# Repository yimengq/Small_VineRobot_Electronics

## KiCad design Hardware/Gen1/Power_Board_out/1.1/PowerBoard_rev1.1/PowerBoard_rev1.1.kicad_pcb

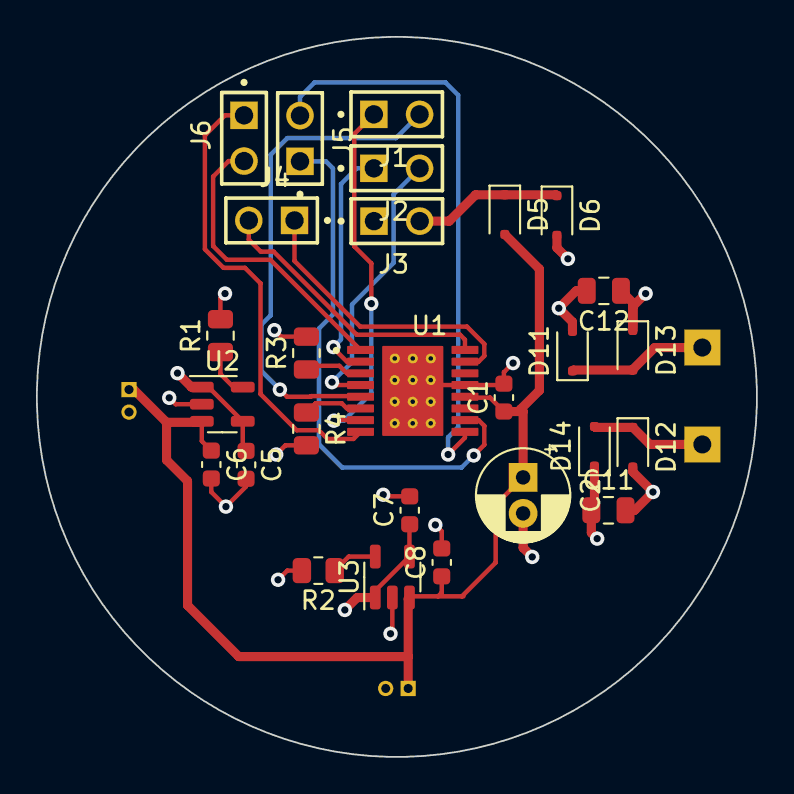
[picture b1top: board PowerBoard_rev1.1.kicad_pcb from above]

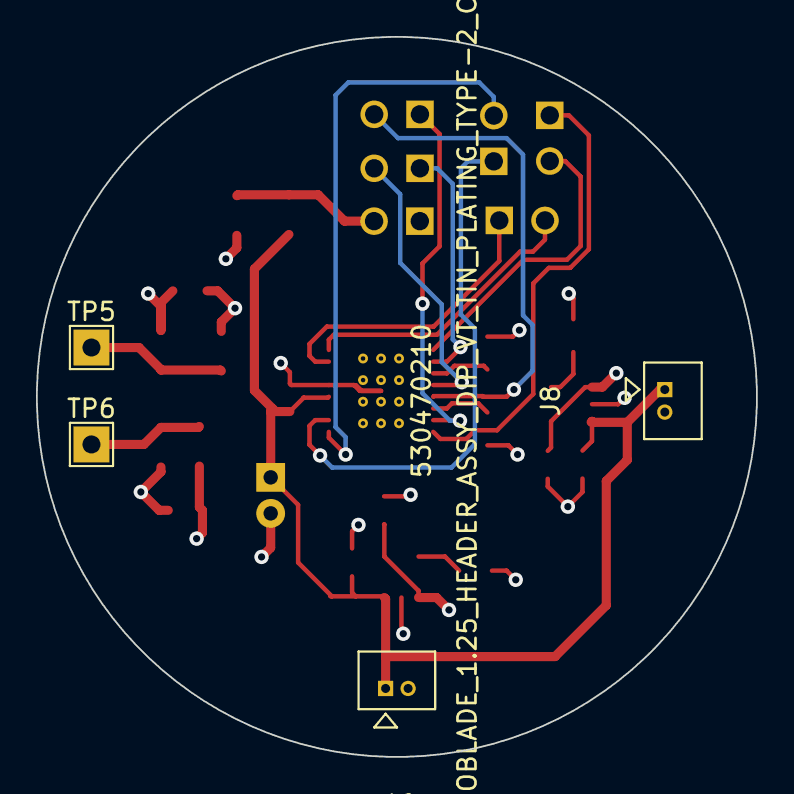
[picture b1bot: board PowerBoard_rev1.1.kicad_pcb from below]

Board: 4 copper layers, 40.0 x 40.0 mm, 31 parts (4 on the bottom side), 20 nets.

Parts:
C1: 100nF; C_0603_1608Metric
C2: 10uF; CP_Radial_D5.0mm_P2.00mm
C5, C6, C7, C8: 1uF; C_0603_1608Metric
C11: 6nF; C_0805_2012Metric
C12: 10uF; C_0805_2012Metric
D5, D6, D11, D12, D13, D14: PMEG6010CEJ; D_SOD-323F
J1, J2, J3, J4, J5, J6: HMTSW-102-X-X-S-X; SAMTEC_HMTSW-102-X-X-S-X
J7, J8: 530470210; CON_530470210_MOL
R1, R2: 2k; R_0805_2012Metric
R3, R4: 2; R_0805_2012Metric
TP5: COIL1; TestPoint_THTPad_2.0x2.0mm_Drill1.0mm
TP6: COIL2; TestPoint_THTPad_2.0x2.0mm_Drill1.0mm
U1: DRV8410PWPR; IC_DRV8410PWPR
U2, U3: MCP73812T-420I-OT; SOT-23-5

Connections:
+BATT: C1.1, C2.1, C6.1, C8.1, D5.2 (A), J7.1, J8.1, U1.12 (VM), U2.3 (V_{BAT}), U3.3 (V_{BAT})
DRV_FAULT: J6.01, U1.8 (~FAULT)
DRV_SLEEP: J6.02, U1.1 (~SLEEP)
GND: C1.2, C2.2, C5.2, C6.2, C7.2, C8.2, C11.2, C12.2, D11.2 (A), D12.2 (A), J3.01, J7.2, J8.2, R1.2, R2.2, R3.2, R4.2, U1.13 (GND), U1.17 (EXP), U2.2 (V_{SS}), U3.2 (V_{SS})
MOTOR1_AIN1: J4.02, U1.16 (AIN1)
MOTOR1_AIN2: J4.01, U1.15 (AIN2)
MOTOR2_BIN1: J5.02, U1.9 (BIN1)
MOTOR2_BIN2: J5.01, U1.10 (BIN2)
unnamed: D11.1 (K), D13.2 (A), TP5.1
unnamed: D12.1 (K), D14.2 (A), TP6.1
unnamed: R3.1, U1.3 (AISEN)
unnamed: J2.01, U1.2 (AOUT1)
unnamed: J2.02, U1.4 (AOUT2)
unnamed: R4.1, U1.6 (BISEN)
unnamed: J1.01, U1.7 (BOUT1)
unnamed: J1.02, U1.5 (BOUT2)
unnamed: R1.1, U2.5 (PROG)
unnamed: R2.1, U3.5 (PROG)
VCC: C5.1, C7.1, C11.1, C12.1, D6.2 (A), D13.1 (K), D14.1 (K), U2.1 (CE), U2.4 (V_{DD}), U3.1 (CE), U3.4 (V_{DD})
VDC: D5.1 (K), D6.1 (K), J3.02

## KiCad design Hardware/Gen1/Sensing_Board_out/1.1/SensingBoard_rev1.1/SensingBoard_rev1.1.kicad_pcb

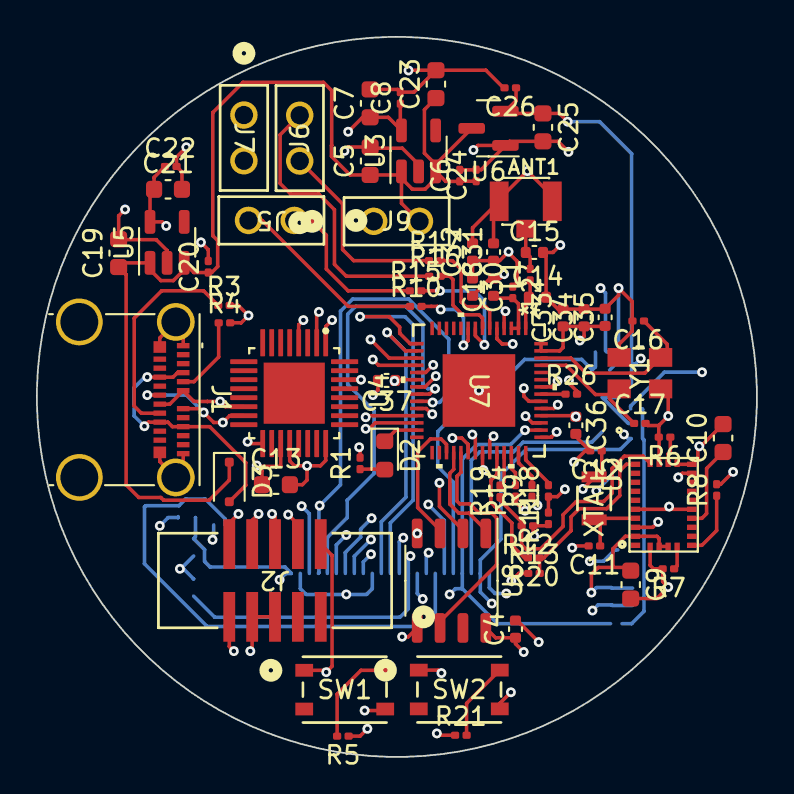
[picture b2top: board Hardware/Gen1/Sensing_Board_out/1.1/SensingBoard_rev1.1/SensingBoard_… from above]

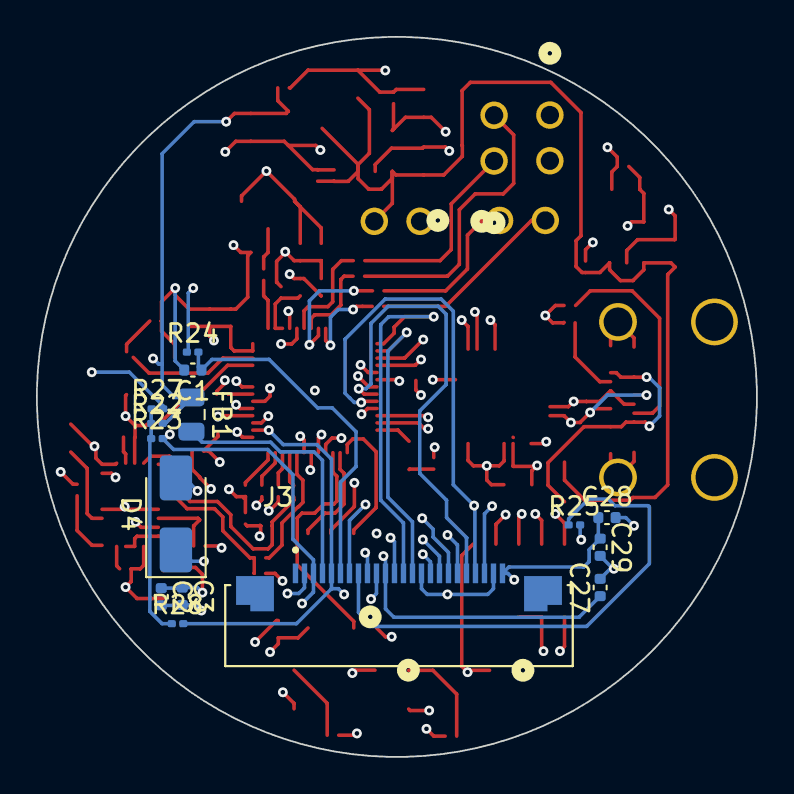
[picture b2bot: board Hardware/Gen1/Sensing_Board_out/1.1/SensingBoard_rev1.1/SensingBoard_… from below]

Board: 6 copper layers, 40.0 x 40.0 mm, 89 parts (15 on the bottom side), 74 nets.

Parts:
ANT1: U.FL-R-SMT-1
C1, C2, C4, C18, C29, C30, C34, C36, C37: 100nF; C_0402_1005Metric
C3: 4.7uF; C_0402_1005Metric
C5, C7, C13, C19, C21, C23, C25: 10uF; C_0603_1608Metric
C6, C8, C20, C22, C24, C26: 1uF; C_0201_0603Metric
C9, C10: 0.1uF; C_0603_1608Metric
C11, C12: 22pF; C_0201_0603Metric
C14, C15: 1.6pF; C_0402_1005Metric
C16, C17: 18pF; C_0201_0603Metric
C27, C28, C31, C32, C33: 2.2uF; C_0402_1005Metric
C35: 10nF; C_0402_1005Metric
D2: LED; LED_0603_1608Metric
D3: PMEG6010CEJ; D_SOD-323F
D4: B140-E3; D_SMA
FB1: 120R-3A; C_0805_2012Metric
J1: USB_C_Receptacle; USB_C_Receptacle_Molex_105450-0101-L
J2: 3221-10-0300-00; CONN10_3221-10-0300-00_CNC
J3: F32R-1A7H1-11024; AMPHENOL_F32R-1A7H1-11024
J5, J6, J7, J9: RS1-02-G; CONN_RS1-02-G_ADM
L1, L2: 2nH; L_0201_0603Metric
R1: 100; R_0201_0603Metric
R3: 6.1K; R_0201_0603Metric
R4: 5.1K; R_0201_0603Metric
R5, R6, R7, R8, R11, R12, R13, R21, R24, R25: 10k; R_0201_0603Metric
R9, R10, R14, R15, R16, R17, R18, R19, R20, R22, R27: 0k; R_0201_0603Metric
R23, R28: 4.7k; R_0201_0603Metric
R26: 499; R_0201_0603Metric
SW1, SW2: PTS815 SJM 250 SMTR LFS; SW4_PTS815 SJM 250 SMTR LFS_CNK
U2: BNO055; LGA28R50P4X10_380X520X100
U3: MIC5504-3.3YM5; SOT-23-5
U4: FT232RQ; QFN50P500X500X90-33N
U5: MIC5504-1.8YM5; SOT-23-5
U6: MCP1700x-280xxTT; SOT-23
U7: ESP32-S3; QFN56_7X7_EXP
U8: GD25D05CT; SOP-8_3.9x4.9mm_P1.27mm
XTAL2: ABS07-32.768KHZ-7-T; XTAL_ABS07-32.768KHZ-7-T_ABR
Y1: ABM8G-40.000MHZ-18-D2Y-T; CRYSTAL_ABM8G_ABR

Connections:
+1V8: C21.1, C22.1, J3.10, U5.5 (VOUT)
+2V8: C25.1, C26.1, C27.1, D4.2 (A), FB1.1, J3.11, R22.2, U6.2 (VO)
+3.3V: C2.1, C3.1, C4.1, C7.1, C8.1, C9.1, C13.1, C30.1, C31.1, C32.1, C33.1, C34.1, C35.1, C36.1, C37.1, J2.5, L2.1, R1.2, R5.1, R11.1, R12.1, R13.1, R21.1, R24.1, R27.2, U2.3 (VDD), U2.4 (NBOOT_LOAD_PIN), U2.28 (VDDIO), U3.5 (VOUT), U4.1 (VCCIO), U4.19 (VCC), U7.20 (VDD3P3_RTC), U7.46 (VDD3P3_CPU), U7.55 (VDDA), U7.56 (VDDA), U8.8 (VCC)
+5V: D3.2 (A), J1.A4 (VBUS), J1.A9 (VBUS), J1.B4 (VBUS), J1.B9 (VBUS)
BNO_INT: R14.1, U2.14 (INT)
BNO_SCL: R12.2, R19.1, U2.19 (COM1)
BNO_SDA: R13.2, R20.1, U2.20 (COM0)
CAM_RESET: C1.1, J3.6, R24.2
CHIP_EN: J2.6, SW1.1, U7.4 (CHIP_PU)
D0/A0: R17.2, U7.6 (GPIO1)
D1/A1: R16.2, U7.7 (GPIO2)
D2/A2: R15.2, U7.8 (GPIO3)
D3/A3: R10.2, U7.9 (GPIO4)
DRV_FAULT: J7.1, R11.2, R18.1
DRV_SLEEP: J7.2, R9.1
GND: ANT1.GND1, ANT1.GND2, C1.2, C2.2, C3.2, C4.2, C5.2, C6.2, C7.2, C8.2, C9.2, C10.2, C11.2, C12.2, C13.2, C14.2, C15.2, C16.2, C17.2, C18.2, C19.2, C20.2, C21.2, C22.2, C23.2, C24.2, C25.2, C26.2, C27.2, C28.2, C29.2, C30.2, C31.2, C32.2, C33.2, C34.2, C35.2, C36.2, C37.2, J1.A1 (GND), J1.A12 (GND), J1.B1 (GND), J1.B12 (GND), J1.S1 (SHIELD), J2.3, J2.4, J3.2, J3.15, J3.23, J9.1, R3.2, R4.2, R6.2, R7.2, R8.2, R25.2, SW1.4, SW2.4, U2.2 (GND), U2.10 (PIN10), U2.15 (PIN15), U2.16 (PIN16), U2.18 (COM2), U2.25 (GNDIO), U3.2 (GND), U4.4 (GND), U4.17 (GND), U4.20 (GND), U4.24 (AGND), U5.2 (GND), U6.1 (GND), U7.57 (GND), U8.4 (VSS), Y1.2 (GND), Y1.4 (GND)
GPIO0: SW2.1, U7.5 (GPIO0)
GPIO33: R20.2, U7.38 (GPIO33)
GPIO34: R19.2, U7.39 (GPIO34)
GPIO35: R14.2, U7.40 (GPIO35)
GPIO36: R9.2, U7.41 (GPIO36)
GPIO37: R18.2, U7.42 (GPIO37)
IO10/XMCLK: J3.13, U7.15 (GPIO10)
IO11/DVP_Y8: J3.14, U7.16 (GPIO11)
IO12/DVP_Y7: J3.16, U7.17 (GPIO12)
IO13/DVP_PCLK: J3.17, U7.18 (GPIO13)
IO14/DVP_Y6: J3.18, U7.19 (GPIO14)
IO15/DVP_Y2: J3.19, U7.21 (XTAL_32K_P)
IO16/DVP_Y5: J3.20, U7.22 (XTAL_32K_N)
IO17/DVP_Y3: J3.21, U7.23 (GPIO17)
IO18/DVP_Y4: J3.22, U7.24 (GPIO18)
IO21/USER_LED: D2.1 (K), U7.27 (GPIO21)
IO38/DVP_VSYNC: J3.7, U7.43 (GPIO38)
IO47/DVP_HREF: J3.9, U7.37 (SPICLK_P)
IO48/DVP_Y9: J3.12, U7.36 (SPICLK_N)
MOTOR1_AIN1: J5.2, R10.1
MOTOR1_AIN2: J5.1, R15.1
MOTOR2_BIN1: J6.2, R16.1
MOTOR2_BIN2: J6.1, R17.1
MTCK/IO39/CAM_SCL: J2.7, J3.5, R28.2, U7.44 (MTCK)
MTDI/IO41/PDM_DATA: J2.9, U7.47 (MTDI)
MTDO/IO40/CAM_SDA: J2.8, J3.3, R23.2, U7.45 (MTDO)
MTMS/IO42/PDM_CLK: J2.10, U7.48 (MTMS)
unnamed: ANT1.SIG, C15.1, L1.2
unnamed: C18.1, L2.2, U7.2 (VDD3P3), U7.3 (VDD3P3)
unnamed: D2.2 (A), R1.1
unnamed: C28.1, C29.1, D4.1 (K), J3.24
unnamed: FB1.2, J3.4
unnamed: J1.A5 (CC1), R4.1
unnamed: J1.B5 (CC2), R3.1
unnamed: J3.8, R25.1
unnamed: R5.2, SW1.2
unnamed: R21.2, SW2.2
unnamed: R22.1, R23.1, R27.1, R28.1
unnamed: C10.1, U2.9 (CAP)
unnamed: R6.1, U2.17 (COM3)
unnamed: R8.1, U2.6 (PS0)
unnamed: R7.1, U2.5 (PS1)
unnamed: C12.1, U2.27 (XIN32), XTAL2.2
unnamed: C11.1, U2.26 (XOUT32), XTAL2.1
unnamed: C14.1, L1.1, U7.1 (LNA_IN)
unnamed: R26.1, U7.49 (U0TXD)
unnamed: C17.1, U7.53 (XTAL_N), Y1.1
unnamed: C16.1, U7.54 (XTAL_P), Y1.3
RX_D7: U4.30 (TXD), U7.50 (U0RXD)
SPICLK: U7.33 (SPICLK), U8.6 (SCLK)
SPICS0: U7.32 (SPICS0), U8.1 (~CS)
SPID: U7.35 (SPID), U8.5 (SI/IO0)
SPIQ: U7.34 (SPIQ), U8.2 (O1/SO)
SPIWP: U7.31 (SPIWP), U8.3 (~WP)
TX_D6: R26.2, U4.2 (RXD)
USB_DN: J1.A7 (D-), J1.B7 (D-), U4.15 (USBDM), U7.25 (GPIO19)
USB_DP: J1.A6 (D+), J1.B6 (D+), U4.14 (USBDP), U7.26 (GPIO20)
VDC: C5.1, C6.1, C19.1, C20.1, C23.1, C24.1, D3.1 (K), J9.2, U3.1 (VIN), U3.3 (EN), U5.1 (VIN), U5.3 (EN), U6.3 (VI)

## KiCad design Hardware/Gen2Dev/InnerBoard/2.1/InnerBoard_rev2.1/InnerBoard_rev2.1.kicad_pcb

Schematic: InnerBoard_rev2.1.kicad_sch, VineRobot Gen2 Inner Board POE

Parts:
C1: 15uF; C_0805_2012Metric; Mfr P/N CL10A106KP8NNNC
C2, C8: 100pF; C_0805_2012Metric; Mfr P/N CL10A106KP8NNNC
C3: 220nF; C_0805_2012Metric; Mfr P/N CL10A106KP8NNNC
C4: 470pF; C_0805_2012Metric; Mfr P/N CL10A106KP8NNNC
C5: 12nF; C_0805_2012Metric; Mfr P/N CL10A106KP8NNNC
C6, C61, C62, C64, C65, C68, C70: 100nF; C_0805_2012Metric; Mfr P/N CL10A106KP8NNNC
C7, C72: 1uF; C_0805_2012Metric; Mfr P/N CL10A106KP8NNNC
C20, C22, C31: 10uF; C_0805_2012Metric; Mfr P/N CL10A106KP8NNNC
C21, C23: 1uF; C_0805_2012Metric; Mfr P/N CC0201MRX5R6BB105
C24, C29: 18pF; C_0402_1005Metric; Mfr P/N CL10A106KP8NNNC
C25, C26: 100nF; C_0805_2012Metric
C27: 10uF; C_0805_2012Metric
C32: 1uF; C_0805_2012Metric
C59, C69: 1nF; C_0805_2012Metric; Mfr P/N CL10A106KP8NNNC
C60, C66, C67, C71: 22uF; C_0805_2012Metric; Mfr P/N CL10A106KP8NNNC
C63: 2.2uF; C_0805_2012Metric; Mfr P/N CL10A106KP8NNNC
D4, D5, D7, D11: LED; LED_0603_1608Metric; Mfr P/N 19-21/GHC-YR1S2/4T
D6: 1N5819; D_DO-41_SOD81_P10.16mm_Horizontal
D10, D13, D14: 1N5819WS; D_SOD-323
D15: BAT54C; SOT-23
D23: SMAJ58A; D_SMA
D24: BAT54A; SOT-23
FID1, FID2, FID3, FID4: Fiducial; Fiducial_0.5mm_Mask1.5mm
H1, H2, H3, H4: MountingHole; MountingHole_2.1mm
J1, J2, J3, J4, J7, J9, J10, J11, J12, J13, J14, J15, J16, J17, J18, J19: HMTSW-102-X-X-S-X; SAMTEC_HMTSW-102-X-X-S-X; PARTREV A
J5: UJ31-CH-G2-SMT-TR; CUI_UJ31-CH-G2-SMT-TR; PART_REV 1.01
J8: 3221-10-0300-00; CONN10_3221-10-0300-00_CNC; Mfr P/N 3221-10-0300-00
J25: SI-46020-F; BEL_SI-46020-F; PARTREV C
JP1: SolderJumper_2_Open; SolderJumper-2_P1.3mm_Open_Pad1.0x1.5mm
L8, L9: 600R/2A; L_0805_2012Metric
MH2, MH3: Mounting_hole_Shield_3.3mm; MountingHole_3.2mm_M3_Pad_Via; not fitted
Q1, Q9: SI2323DS-T1-GE3; SOT23
Q4, Q5: BC817; SOT-23
Q10: BSS138; SOT-23
R1: 130k; R_0805_2012Metric; Mfr P/N AC0201FR-07100RL
R2, R21, R30, R97, R100, R101: 10k; R_0805_2012Metric; Mfr P/N AC0201FR-07100RL
R3: 18k; R_0805_2012Metric; Mfr P/N AC0201FR-07100RL
R4: 8.25k; R_0805_2012Metric; Mfr P/N AC0201FR-07100RL
R5: 9.3k; R_0805_2012Metric; Mfr P/N AC0201FR-07100RL
R6: 6k; R_0805_2012Metric; Mfr P/N AC0201FR-07100RL
R7, R23, R25, R28, R51: 100; R_0805_2012Metric; Mfr P/N AC0201FR-07100RL
R8: 5.24M; R_0805_2012Metric; Mfr P/N AC0201FR-07100RL
R22, R29, R104, R105, R106, R107: 2.2k; R_0805_2012Metric; Mfr P/N AC0201FR-07100RL
R24: 0; R_0805_2012Metric; not fitted
R26, R42, R47, R52: 10k; R_0805_2012Metric
R27: 5.1K; R_0805_2012Metric; Mfr P/N RC0201FR-075K1L
R31: 12.1k; R_0805_2012Metric; Mfr P/N AC0201FR-07100RL
R32, R99: 1k; R_0805_2012Metric; Mfr P/N AC0201FR-07100RL
R33, R81, R82, R83: 49.9; R_0805_2012Metric; Mfr P/N AC0201FR-07100RL
R34, R43: 2.2k; R_0805_2012Metric
R35: 10; R_0805_2012Metric
R41, R45: 1k; R_0805_2012Metric
R46, R49: 220; R_0805_2012Metric
R50: 5.1K; R_0805_2012Metric; Mfr P/N RC0201DR-076K04L
R84, R89: 220; R_0805_2012Metric; Mfr P/N AC0201FR-07100RL
R90: 24.9k; R_0805_2012Metric; Mfr P/N AC0201FR-07100RL
R93: 180k; R_0805_2012Metric; Mfr P/N AC0201FR-07100RL
R94: 4.42k; R_0805_2012Metric; Mfr P/N AC0201FR-07100RL
R108: 49.9k; R_0805_2012Metric; Mfr P/N AC0201FR-07100RL
R109: 100k; R_0805_2012Metric; Mfr P/N AC0201FR-07100RL
SW1: PTS815 SJM 250 SMTR LFS; SW4_PTS815 SJM 250 SMTR LFS_CNK; Mfr P/N PTS815SJG250SMTRLFS
TP1, TP2, TP3, TP4, TP5, TP6, TP8, TP9, TP10, TP11, TP12, TP13, TP14, TP15, TP16, TP18, TP19, TP20, TP21, TP22, TP23, TP24, TP25, TP26, TP27, TP28, TP29, TP30: TestPoint; TestPoint_Pad_D2.0mm
U1: LM5156DSSR; DSS0012B
U4: MIC5504-3.3YM5; SOT-23-5; Mfr P/N MIC5504-3.3YM5-TR
U6: 74LVC1G04; SOT-23-5
U7: LD1117S50TR_SOT223; SOT-223-3_TabPin2
U9: FT232RQ; QFN50P500X500X90-33N; Mfr P/N FT232RQ-REEL
U10: ESP32-WROOM-32E-N8; ESP32­WROOM­32E_EXP
U11: LAN8710A-EZC; QFN32_5X5MC_MCH
U12: TPS2376PW; PW8
U23: ESDS314DBVR; DBV0005A_N
U25: MCP100-270D; TO127P254X495-3
Y1: ABLS2-12.000MHZ-D4Y-T; XTAL_ABLS2-12.000MHZ-D4Y-T; PARTREV 11.15.2016
Y3: ASV-50.000MHZ-LCS-T; XTAL_ASV-50.000MHZ-LCS-T; PARTREV 09.02.14

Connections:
+3.3V: C22.1, C23.1, C31.1, C71.1, D24.1, J4.01, J8.10, J9.02, L9.1, Q9.2, R23.2, R26.1, R34.1, R42.1, R43.1, R47.1, R52.1, R97.2, R100.1, TP23.1, U10.2 (3V3), Y3.4 (VDD)
+3.3VLAN: C25.1, C65.1, C66.1, C67.1, J10.01, L8.2, L9.2, Q9.3, R22.2, R29.2, R30.2, R107.1, TP16.1, U6.3 (GND)
+5V: C20.1, C21.1, C27.1, D6.1 (K), J3.01, Q1.2, R25.2, R28.2, TP21.1, U7.2 (VO)
+5VP: D6.2 (A), J2.01, Q1.1, R21.2, TP19.1
+9V: C26.1, TP22.1, U7.3 (VI)
D_Com: D15.3, R24.1, R46.1, TP13.1
ESP_EN: C32.1, D10.2 (A), D24.2, R52.2, R109.1, TP15.1, U10.3 (EN); also elsewhere on the board
GPI35: U10.7 (IO35)
GPI36/U1RXD: J8.2, R47.2, U10.4 (SENSOR_VP)
GPI39: U10.5 (SENSOR_VN)
GPIO0: D15.1, TP29.1, U6.2, U10.25 (IO0)
GPIO0/XTAL1/CLKIN: R101.1, U11.5 (XTAL1/CLKIN)
GPIO1/U0TXD: D14.1 (K), U10.35 (TXD0)
GPIO2/HS2_DATA0: D15.2, J8.4, TP28.1, U10.24 (IO2)
GPIO3/U0RXD: D13.2 (A), U10.34 (RXD0)
GPIO4/U1TXD: J8.9, U10.26 (IO4)
GPIO5/SPI_CS: J8.5, R42.2, TP30.1, U10.29 (IO5)
GPIO12/PHY_PWR: TP26.1, U10.14 (IO12)
GPIO13/I2C-SDA: J8.3, R43.2, U10.16 (IO13)
GPIO14/HS2_CLK: J8.6, U10.13 (IO14)
GPIO15/HS2_CMD: J8.7, TP27.1, U10.23 (IO15)
GPIO16/I2C-SCL: R35.1, U10.27 (IO16)
GPIO17/EMAC_CLK_OUT_180: U6.4, U10.28 (IO17)
GPIO18/MDIO(RMII): R22.1, U10.30 (IO18), U11.16 (MDIO)
GPIO19/EMAC_TXD0(RMII): U10.31 (IO19), U11.22 (TXD0)
GPIO21/EMAC_TX_EN(RMII): U10.33 (IO21), U11.21 (TXEN)
GPIO22/EMAC_TXD1(RMII): U10.36 (IO22), U11.23 (TXD1)
GPIO23/MDC(RMII): U10.37 (IO23), U11.17 (MDC)
GPIO25/EMAC_RXD0(RMII): U10.10 (IO25), U11.11 (RXD0/*MODE0)
GPIO26/EMAC_RXD1(RMII): U10.11 (IO26), U11.10 (RXD1/*MODE1)
GPIO27/EMAC_RX_CRS_DV: R29.1, U10.12 (IO27), U11.15 (COL/CRS_DV/*MODE2)
GPIO32: U10.8 (IO32)
GPIO33: R35.2, U10.9 (IO33)
LED1: U11.3 (LED1/*REGOFF); also elsewhere on the board
LED2: U11.2 (LED2/*NINTSEL); also elsewhere on the board
unnamed: C4.2, C5.2, R6.2
unnamed: C71.2, Q9.1, R97.1, R99.2, TP9.1
unnamed: D4.2 (A), R25.1
unnamed: D5.2 (A), R23.1
unnamed: D7.2 (A), R28.1
unnamed: D10.1 (K), Q4.3 (C)
unnamed: D11.2 (A), R51.1
unnamed: D13.1 (K), TP1.1, U9.30 (TXD)
unnamed: D14.2 (A), TP2.1, U9.2 (RXD)
unnamed: D24.3, R108.1
unnamed: J5.A5 (CC1), R27.1, TP3.1
unnamed: J5.B5 (CC2), R50.1, TP4.1
unnamed 47: C69.1; also elsewhere on the board
unnamed 48: R84.1; also elsewhere on the board
unnamed 49: R89.2; also elsewhere on the board
unnamed 50: J17.02, R81.1, U23.4 (I_O3); also elsewhere on the board
unnamed 51: J16.02, R33.1, U23.5 (I_O4); also elsewhere on the board
unnamed 52: J19.01, R83.1, U23.1 (I_O1); also elsewhere on the board
unnamed 53: R82.1, U11.28 (TXN), U23.3 (I_O2); also elsewhere on the board
unnamed: J8.8, R34.2
unnamed: J13.02, R104.1
unnamed: J14.02, R105.1
unnamed: J15.02, R106.1
unnamed: J18.01, J19.02
unnamed: C59.1, JP1.2 (B), R30.1, R32.2, U11.19 (NRST)
unnamed: Q4.1 (B), R41.1
unnamed: Q4.2 (E), R45.2, U9.32 (~RTS)
unnamed: Q5.1 (B), R45.1
unnamed: Q5.3 (C), R41.2, U9.31 (~DTR)
unnamed: Q5.2 (E), R46.2
unnamed: Q10.3 (D), R99.1
unnamed: R7.1, R8.2
unnamed: R24.2, R26.2, SW1.2
unnamed: C4.1, C5.1, U1.6 (COMP)
unnamed: C8.1, R7.2, U1.5 (CS)
unnamed: C7.1, U1.2 (VCC), U1.7 (DITHOFF)
unnamed: R5.2, U1.10 (RT)
unnamed: C3.1, U1.9 (SS)
unnamed: C2.1, R3.1, R4.2, U1.12 (UVLO_SYNC)
unnamed: J3.02, U4.1 (VIN), U4.3 (EN)
unnamed: J9.01, U4.5 (VOUT)
unnamed: C24.2, U9.27 (OSCI), Y1.2
unnamed: C29.2, U9.28 (OSCO), Y1.1
unnamed: J11.02, U9.15 (USBDM)
unnamed: J12.02, U9.14 (USBDP)
unnamed: J4.02, U9.1 (VCCIO), U9.19 (VCC)
unnamed: C60.1, C61.1, C62.2, TP12.1, U11.33 (EPAD)
unnamed: R31.2, U11.32 (RBIAS)
unnamed: J16.01, U11.30 (RXN)
unnamed: J17.01, U11.31 (RXP)
unnamed: J18.02, U11.29 (TXP)
unnamed: J7.01, U11.27 (VDD1A)
unnamed: J1.02, U11.1 (VDD2A)
unnamed: C63.1, C64.1, U11.6 (VDDCR)
unnamed: J10.02, U11.12 (VDDIO)
unnamed: R94.2, U12.2 (CLASS)
unnamed: R90.1, U12.3 (DET)
unnamed: R93.2, U12.1 (ILIM)
unnamed: R1.1, R2.2, TP18.1, U12.7 (UVLO)
unnamed: C72.1, R108.2, R109.2, TP25.1, U25.2 (VDD)
unnamed: R101.2, Y3.3 (OUTPUT)
OSC_DIS: Q10.1 (G), R32.1, R100.2, TP8.1, U25.1 (~RST), Y3.1 (TRI_STATE)
PHYAD0: J13.01, U11.13 (RXER/RXD4/*PHYAD0)
PHYAD1: J14.01, U11.7 (RXCLK/*PHYAD1)
PHYAD2: J15.01, U11.8 (RXD3/*PHYAD2)
RMIISEL: R107.2, TP24.1, U11.9 (RXD2/*RMIISEL)
Spare1: C1.1, C6.1, C70.1, D23.1 (A1), R1.2, R3.2, R90.2, TP11.1, U1.1 (BIAS), U12.8 (VDD); also elsewhere on the board
USB_DN: J5.A7 (DN1), J5.B7 (DN2), J11.01, TP5.1
USB_DP: J5.A6 (DP1), J5.B6 (DP2), J12.01, TP6.1
VBUS: J5.A4 (VBUS), J5.A9 (VBUS__1), J5.B4 (VBUS__2), J5.B9 (VBUS__3), Q1.3, R51.2, TP20.1
VDDA1/2: C60.2, C61.2, C62.1, C68.1, J1.01, J7.02, L8.1, R33.2, R81.2, R82.2, R83.2, R84.2, TP14.1; also elsewhere on the board

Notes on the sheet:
Ethernet
Pin
GPIO15/MTDO
Default
Debugging Log on U0TXD During Booting
Software Selectable Pins
GPIO0:
Internal Bootstrapping Resistors
General Purpose SPI
I2CEXT0_SCL_in
Rising-edge:Output
Pull-Down
3v3 LDO
JTAG
Interface
I2CEXT0_SDA_out
Pull-Up
HSPICLK_in/_out
MTDI/GPIO12:
Don't-care
VSPICLK_in/_out
Any GPIO
EMAC_COL_out
U0TXD Toggling
Falling-edge:Output
3.3V
HSPI_CS1_out
EMAC_MDI_in
HSPIQ_in/_out
VSPI_CS1_out
Rising-edge:Input
9V->5V LDO
1.8V
ESP32-WROOM
Fiducials
Download Boot
GPIO2:
EMAC
MTDO/GPIO15:
U0TXD Silent

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
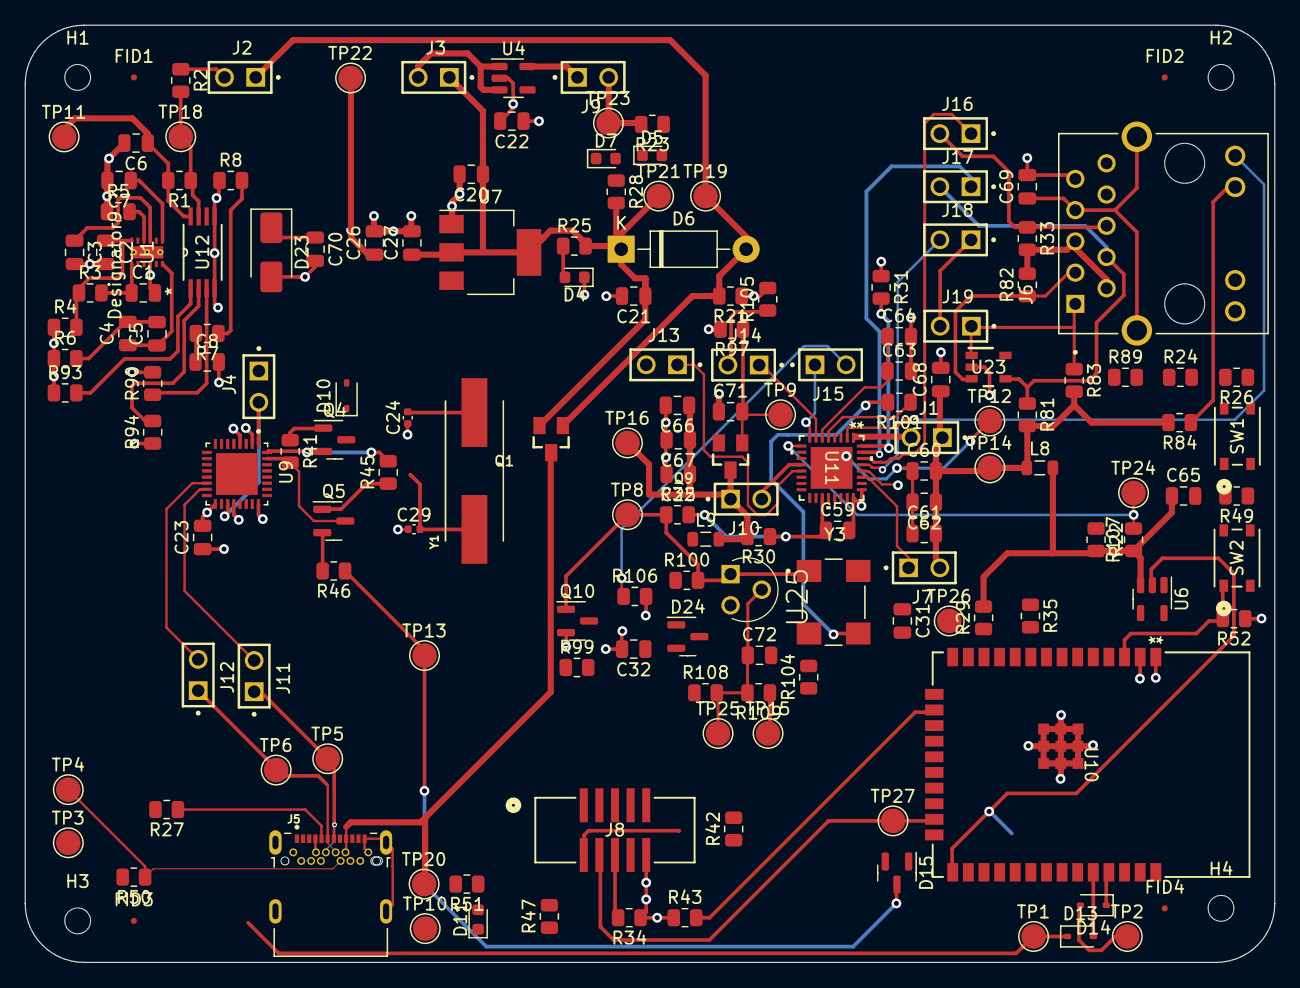
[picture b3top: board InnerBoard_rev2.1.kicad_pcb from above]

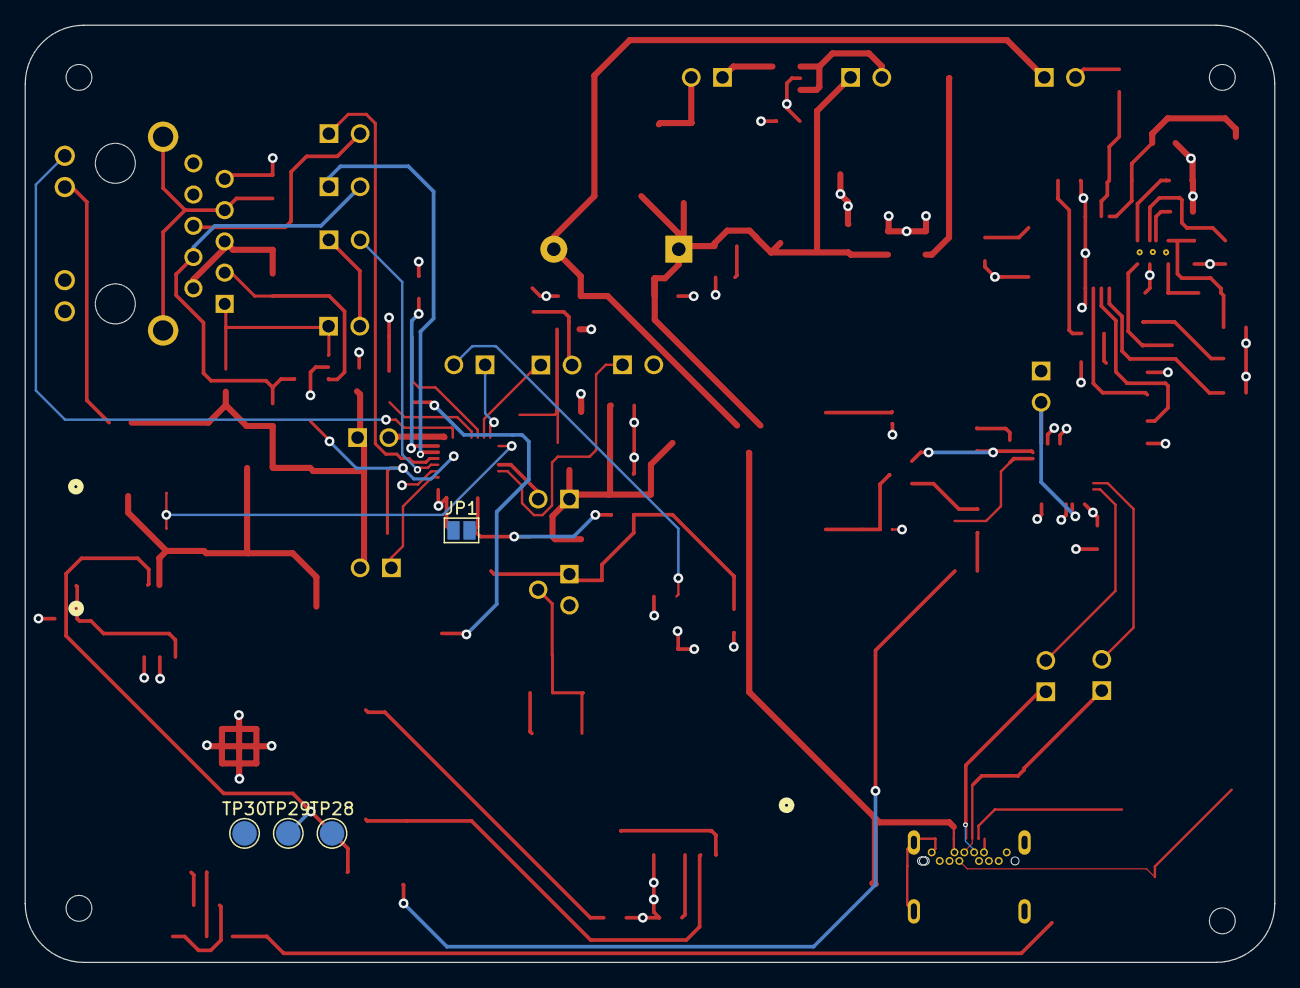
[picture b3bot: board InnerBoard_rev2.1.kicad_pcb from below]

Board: 4 copper layers, 101.6 x 76.2 mm, 172 parts (4 on the bottom side), 106 nets.

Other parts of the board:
J6: SI-46020-F; BEL_SI-46020-F
SW2: PTS815 SJM 250 SMTR LFS; SW4_PTS815 SJM 250 SMTR LFS_CNK

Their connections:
ESP_EN: SW2.1; also elsewhere on the board
LED1: J6.GA1; also elsewhere on the board
LED2: J6.GK2; also elsewhere on the board
unnamed 47: J6.7, J6.S1 (SHIELD), J6.S2 (SHIELD); also elsewhere on the board
unnamed 48: J6.GA2; also elsewhere on the board
unnamed 49: J6.GK1; also elsewhere on the board
unnamed 50: J6.4 (RD+); also elsewhere on the board
unnamed 51: J6.6 (RD-); also elsewhere on the board
unnamed 52: J6.1 (TD+); also elsewhere on the board
unnamed 53: J6.3 (TD-); also elsewhere on the board
Spare1: J6.10; also elsewhere on the board
VDDA1/2: J6.2 (TCT), J6.5 (RCT); also elsewhere on the board

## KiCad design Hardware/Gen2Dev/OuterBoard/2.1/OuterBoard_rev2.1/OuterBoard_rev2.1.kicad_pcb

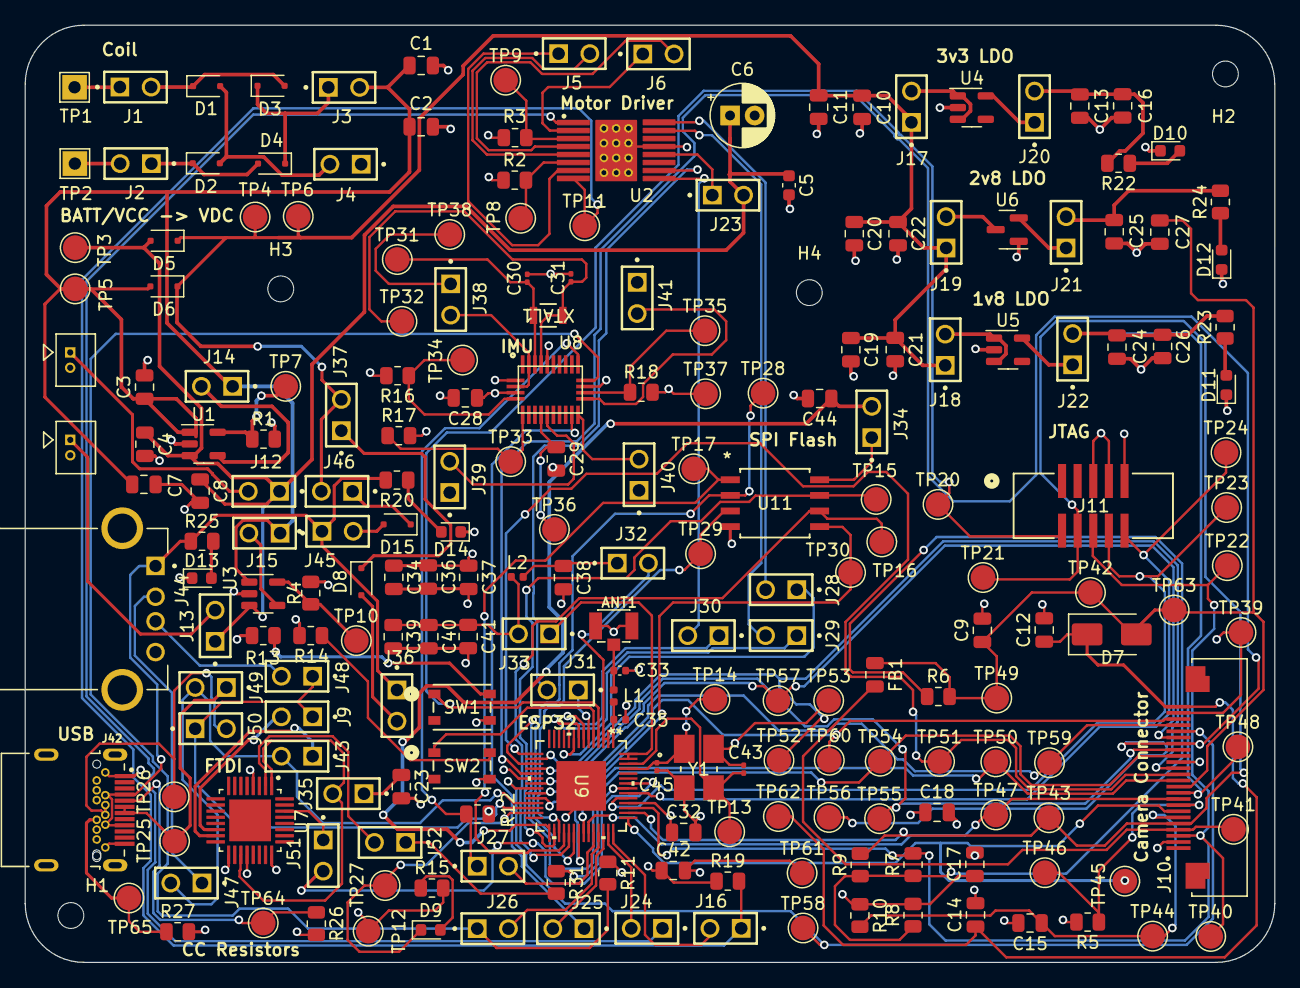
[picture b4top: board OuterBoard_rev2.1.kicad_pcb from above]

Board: 4 copper layers, 101.6 x 76.2 mm, 224 parts (0 on the bottom side), 129 nets.

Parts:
ANT1: U.FL-R-SMT-1
C1: 6nF; C_0805_2012Metric
C2, C10, C13, C19, C20, C23, C24, C25: 10uF; C_0805_2012Metric
C3, C4, C7, C8, C11, C16, C21, C22, C26, C27: 1uF; C_0805_2012Metric
C5: 100nF; C_0603_1608Metric
C6: 10uF; CP_Radial_D5.0mm_P2.00mm
C9, C12, C34, C36, C39: 2.2uF; C_0805_2012Metric
C14, C15, C17, C32, C37, C38, C40, C42, C44: 100nF; C_0805_2012Metric
C18: 4.7uF; C_0805_2012Metric
C28, C29: 0.1uF; C_0805_2012Metric
C30, C31: 22pF; C_0201_0603Metric
C33, C35: 1.6pF; C_0402_1005Metric
C41: 10nF; C_0805_2012Metric
C43, C45: 18pF; C_0201_0603Metric
D1, D2, D3, D4, D5, D6, D8, D15: PMEG6010CEJ; D_SOD-323F
D7: B140-E3; D_SMA
D9, D10, D11, D12, D13, D14: LED; LED_0603_1608Metric
FB1: 120R-3A; C_0805_2012Metric
H1, H2, H3, H4: MountingHole; MountingHole_2.1mm
J1, J2, J3, J4, J5, J6, J9, J12, J13, J14, J15, J16, J17, J18, J19, J20, J21, J22, J23, J24, J25, J26, J27, J28, J29, J30, J31, J32, J33, J34, J35, J36, J37, J38, J39, J40, J41, J43, J45, J46, J47, J48, J49, J50, J51, J52: HMTSW-102-X-X-S-X; SAMTEC_HMTSW-102-X-X-S-X
J7, J8: 530470210; CON_530470210_MOL
J10: F32R-1A7H1-11024; AMPHENOL_F32R-1A7H1-11024
J11: 3221-10-0300-00; CONN10_3221-10-0300-00_CNC
J42: UJ31-CH-G2-SMT-TR; CUI_UJ31-CH-G2-SMT-TR
J44: 87520-0010BLF; AMPHENOL_87520-0010BLF
L1, L2: 2nH; L_0402_1005Metric
R1, R4: 2k; R_0805_2012Metric
R2, R3: 2; R_0805_2012Metric
R5, R10, R11, R12, R13, R14, R16, R17, R18, R19: 10k; R_0805_2012Metric
R6, R8: 0k; R_0805_2012Metric
R7, R9: 4.7k; R_0805_2012Metric
R15, R20, R22, R23, R24, R25: 100; R_0805_2012Metric
R26: 5.1K; R_0805_2012Metric
R27: 6.1K; R_0805_2012Metric
R31: 499; R_0805_2012Metric
SW1, SW2: PTS815 SJM 250 SMTR LFS; SW4_PTS815 SJM 250 SMTR LFS_CNK
TP1: COIL1; TestPoint_THTPad_2.0x2.0mm_Drill1.0mm
TP2: COIL2; TestPoint_THTPad_2.0x2.0mm_Drill1.0mm
TP3, TP4, TP5, TP6, TP7, TP8, TP9, TP10, TP11, TP12, TP13, TP14, TP15, TP16, TP17, TP20, TP21, TP22, TP23, TP24, TP25, TP26, TP27, TP28, TP29, TP30, TP31, TP32, TP33, TP34, TP35, TP36, TP37, TP38, TP39, TP40, TP41, TP42, TP43, TP44, TP45, TP46, TP47, TP48, TP49, TP50, TP51, TP52, TP53, TP54, TP55, TP56, TP57, TP58, TP59, TP60, TP61, TP62, TP63, TP64, TP65: TestPoint; TestPoint_Pad_D2.0mm
U1, U3: MCP73812T-420I-OT; SOT-23-5
U2: DRV8410PWPR; IC_DRV8410PWPR
U4: MIC5504-3.3YM5; SOT-23-5
U5: MIC5504-1.8YM5; SOT-23-5
U6: MCP1700x-280xxTT; SOT-23
U7: FT232RQ; QFN50P500X500X90-33N
U8: BNO055; LGA28R50P4X10_380X520X100
U9: ESP32-S3; QFN56_7X7_EXP
U11: GD25Q64CSIGR; SOP8_208MIL_GDV
XTAL1: ABS07-32.768KHZ-7-T; XTAL_ABS07-32.768KHZ-7-T_ABR
Y1: ABM8G-40.000MHZ-18-D2Y-T; CRYSTAL_ABM8G_ABR

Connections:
+1V8: C24.1, C26.1, J10.10, J22.02, R23.2, TP48.1
+2V8: C9.1, C27.1, D7.2 (A), FB1.1, J10.11, R6.2, TP42.1, TP49.1, TP63.1
+3.3V: C13.1, C16.1, C17.1, C18.1, C23.1, C28.1, C32.1, C34.1, C36.1, C37.1, C39.1, C40.1, C41.1, C42.1, J11.5, J20.02, J33.02, J35.01, J38.01, L2.1, R8.2, R10.1, R11.1, R12.1, R13.1, R14.1, R15.2, R19.1, R22.2, TP12.1, TP38.1, U8.4 (NBOOT_LOAD_PIN), U9.20 (VDD3P3_RTC), U9.46 (VDD3P3_CPU)
+5V: J36.01, J42.A4 (VBUS), J42.A9 (VBUS__1), J42.B4 (VBUS__2), J42.B9 (VBUS__3), J44.1 (VCC), J45.01, R20.2, R25.2
+BATT: C4.1, C5.1, C6.1, C8.1, D5.2 (A), J12.01, J13.01, J23.02, TP3.1, U1.3 (V_{BAT}), U3.3 (V_{BAT})
BNO_INT: J25.01, U8.14 (INT)
BNO_SCL: J26.01, R11.2, U8.19 (COM1)
BNO_SDA: J27.01, R12.2, U8.20 (COM0)
CAM_RESET: C15.1, J10.6, R10.2, TP44.1
CHIP_EN: J11.6, SW1.1, TP20.1, U9.4 (CHIP_PU)
D0/A0: J31.01, U9.6 (GPIO1)
D1/A1: J30.01, U9.7 (GPIO2)
D2/A2: J29.01, U9.8 (GPIO3)
D3/A3: J28.01, U9.9 (GPIO4)
DRV_FAULT: J16.01, R19.2, TP11.1, U2.8 (~FAULT)
DRV_SLEEP: J24.01, U2.1 (~SLEEP)
GND: ANT1.GND1, ANT1.GND2, C1.2, C2.2, C3.2, C4.2, C5.2, C6.2, C7.2, C8.2, C9.2, C10.2, C11.2, C12.2, C13.2, C14.2, C15.2, C16.2, C17.2, C18.2, C19.2, C20.2, C21.2, C22.2, C23.2, C24.2, C25.2, C26.2, C27.2, C28.2, C29.2, C30.2, C31.2, C32.2, C33.2, C34.2, C35.2, C36.2, C37.2, C38.2, C39.2, C40.2, C41.2, C42.2, C43.2, C44.2, C45.2, D10.1 (K), D11.1 (K), D12.1 (K), D13.1 (K), D14.1 (K), J4.01, J7.2, J8.2, J10.2, J10.15, J10.23, J11.3, J11.4, J39.01, J40.01, J41.01, J42.A1 (GND), J42.A12 (GND__1), J42.B1 (GND__2), J42.B12 (GND__3), J42.SH1 (SHIELD), J42.SH2 (SHIELD__1), J42.SH3 (SHIELD__2), J42.SH4 (SHIELD__3), J44.4 (GND), J44.SH1 (SHIELD), J44.SH2 (SHIELD__1), R1.2, R2.2, R3.2, R4.2, R5.2, R16.2, R17.2, R18.2, R26.2, R27.2, SW1.4, SW2.4, TP37.1, TP39.1, TP53.1, TP61.1, U1.2 (V_{SS}), U2.13 (GND), U2.17 (EXP), U3.2 (V_{SS}), U4.2 (GND), U5.2 (GND), U6.1 (GND), U7.4 (GND), U7.17 (GND), U7.20 (GND), U7.24 (AGND), U8.2 (GND), U8.18 (COM2), U8.25 (GNDIO), U9.57 (GND), U11.4 (VSS), Y1.2 (GND), Y1.4 (GND)
GPIO0: SW2.1, U9.5 (GPIO0)
GPIO33: J27.02, U9.38 (GPIO33)
GPIO34: J26.02, U9.39 (GPIO34)
GPIO35: J25.02, U9.40 (GPIO35)
GPIO36: J24.02, U9.41 (GPIO36)
GPIO37: J16.02, U9.42 (GPIO37)
IO10/XMCLK: J10.13, TP51.1, U9.15 (GPIO10)
IO11/DVP_Y8: J10.14, TP52.1, U9.16 (GPIO11)
IO12/DVP_Y7: J10.16, TP54.1, U9.17 (GPIO12)
IO13/DVP_PCLK: J10.17, TP55.1, U9.18 (GPIO13)
IO14/DVP_Y6: J10.18, TP56.1, U9.19 (GPIO14)
IO15/DVP_Y2: J10.19, TP57.1, U9.21 (XTAL_32K_P)
IO16/DVP_Y5: J10.20, TP58.1, U9.22 (XTAL_32K_N)
IO17/DVP_Y3: J10.21, TP59.1, U9.23 (GPIO17)
IO18/DVP_Y4: J10.22, TP60.1, U9.24 (GPIO18)
IO21/USER_LED: D9.1 (K), TP27.1, U9.27 (GPIO21)
IO38/DVP_VSYNC: J10.7, TP45.1, U9.43 (GPIO38)
IO47/DVP_HREF: J10.9, TP47.1, U9.37 (SPICLK_P)
IO48/DVP_Y9: J10.12, TP50.1, U9.36 (SPICLK_N)
MOTOR1_AIN1: J28.02, U2.16 (AIN1)
MOTOR1_AIN2: J29.02, U2.15 (AIN2)
MOTOR2_BIN1: J30.02, U2.9 (BIN1)
MOTOR2_BIN2: J31.02, U2.10 (BIN2)
MTCK/IO39/CAM_SCL: J10.5, J11.7, R9.2, TP21.1, TP43.1, U9.44 (MTCK)
MTDI/IO41/PDM_DATA: J11.9, TP23.1, U9.47 (MTDI)
MTDO/IO40/CAM_SDA: J10.3, J11.8, R7.2, TP22.1, TP40.1, U9.45 (MTDO)
MTMS/IO42/PDM_CLK: J11.10, TP24.1, U9.48 (MTMS)
unnamed: ANT1.SIG, C33.1, L1.2
unnamed: C25.1, J21.02, R24.2
unnamed: C38.1, J32.01, L2.2
unnamed: D1.2 (A), D2.2 (A), J4.02
unnamed: D1.1 (K), D3.2 (A), J1.02
unnamed: D2.1 (K), D4.2 (A), J2.01
unnamed: D3.1 (K), D4.1 (K), J3.01
unnamed: C12.1, C14.1, D7.1 (K), J10.24, TP62.1
unnamed: D8.2 (A), J36.02
unnamed: D8.1 (K), J37.01
unnamed: D9.2 (A), R15.1
unnamed: D10.2 (A), R22.1
unnamed: D11.2 (A), R23.1
unnamed: D12.2 (A), R24.1
unnamed: D13.2 (A), R25.1
unnamed: D14.2 (A), R20.1
unnamed: D15.2 (A), J45.02
unnamed: D15.1 (K), J46.01
unnamed: FB1.2, J10.4, TP41.1
unnamed: J1.01, TP1.1
unnamed: J2.02, TP2.1
unnamed: J10.8, R5.1, TP46.1
unnamed: J7.1, J12.02
unnamed: J8.1, J13.02
unnamed: J32.02, U9.2 (VDD3P3), U9.3 (VDD3P3)
unnamed: J33.01, U9.55 (VDDA), U9.56 (VDDA)
unnamed: J42.A5 (CC1), R26.1, TP64.1
unnamed: J42.B5 (CC2), R27.1, TP65.1
unnamed: J42.A6 (DP1), J42.A7 (DN1), J49.01, TP25.1
unnamed: J42.B6 (DP2), J42.B7 (DN2), J50.02, TP26.1
unnamed: J44.3 (D+), J48.02
unnamed: J44.2 (D-), J47.01
unnamed: R6.1, R7.1, R8.1, R9.1
unnamed: R13.2, SW1.2
unnamed: R14.2, SW2.2
unnamed: R1.1, TP7.1, U1.5 (PROG)
unnamed: J14.02, U1.4 (V_{DD})
unnamed: R3.1, TP9.1, U2.3 (AISEN)
unnamed: J6.01, U2.2 (AOUT1)
unnamed: J6.02, U2.4 (AOUT2)
unnamed: R2.1, TP8.1, U2.6 (BISEN)
unnamed: J5.01, U2.7 (BOUT1)
unnamed: J5.02, U2.5 (BOUT2)
unnamed: J23.01, U2.12 (VM)
unnamed: R4.1, TP10.1, U3.5 (PROG)
unnamed: J15.02, U3.4 (V_{DD})
unnamed: J17.02, U4.1 (VIN), U4.3 (EN)
unnamed: J20.01, U4.5 (VOUT)
unnamed: J18.02, U5.1 (VIN), U5.3 (EN)
unnamed: J22.01, U5.5 (VOUT)
unnamed: J19.02, U6.3 (VI)
unnamed: J21.01, U6.2 (VO)
unnamed: J52.02, U7.2 (RXD)
unnamed: J51.01, U7.30 (TXD)
unnamed: J43.01, U7.15 (USBDM)
unnamed: J9.02, U7.14 (USBDP)
unnamed: J35.02, U7.1 (VCCIO), U7.19 (VCC)
unnamed: C29.1, TP36.1, U8.9 (CAP)
unnamed: R18.1, TP35.1, U8.17 (COM3)
unnamed: J39.02, U8.10 (PIN10)
unnamed: J40.02, U8.15 (PIN15)
unnamed: J41.02, U8.16 (PIN16)
unnamed: R17.1, TP33.1, U8.6 (PS0)
unnamed: R16.1, TP34.1, U8.5 (PS1)
unnamed: J38.02, U8.3 (VDD), U8.28 (VDDIO)
unnamed: C30.1, TP31.1, U8.27 (XIN32), XTAL1.2
unnamed: C31.1, TP32.1, U8.26 (XOUT32), XTAL1.1
unnamed: C35.1, L1.1, U9.1 (LNA_IN)
unnamed: R31.1, U9.49 (U0TXD)
unnamed: C45.1, TP14.1, U9.53 (XTAL_N), Y1.1
unnamed: C43.1, TP13.1, U9.54 (XTAL_P), Y1.3
unnamed: J34.01, U11.8 (VCC)
RX_D7: J51.02, U9.50 (U0RXD)
SPICLK: TP16.1, U9.33 (SPICLK), U11.6 (SCLK)
SPICS0: TP17.1, U9.32 (SPICS0), U11.1 (CS#)
SPID: TP30.1, U9.35 (SPID), U11.5 (SI(IO0))
SPIHD: TP15.1, U9.30 (SPIHD), U11.7 (HOLD#(IO3))
SPIQ: TP28.1, U9.34 (SPIQ), U11.2 (SO(IO1))
SPIWP: TP29.1, U9.31 (SPIWP), U11.3 (WP#(IO2))
TX_D6: J52.01, R31.2
USB_DN: J43.02, J47.02, J49.02, U9.25 (GPIO19)
USB_DP: J9.01, J48.01, J50.01, U9.26 (GPIO20)
VCC: C1.1, C2.1, C3.1, C7.1, D6.2 (A), J3.02, J14.01, J15.01, TP5.1, U1.1 (CE), U3.1 (CE)
VDC: C10.1, C11.1, C19.1, C20.1, C21.1, C22.1, D5.1 (K), D6.1 (K), J17.01, J18.01, J19.01, J37.02, J46.02, TP4.1, TP6.1
VDD_SPI: C44.1, J34.02, U9.29 (VDD_SPI)
